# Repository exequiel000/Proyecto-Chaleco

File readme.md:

# VitalVest — Firmware (ESP32), pruebas y conexión con la app

Chaleco inteligente corrector de postura con monitoreo de **inclinación (grados)**, **pulsaciones (BPM)** y **temperatura (°C)**, conectado por Bluetooth (BLE) a la app VitalVest.

---

## 1. Cómo usar los códigos (Arduino IDE)

1. Descomprimir. Cada carpeta es un sketch: abrir el `.ino` que está adentro.
2. `Herramientas > Placa`: **ESP32 Dev Module**. Elegir el puerto COM.
3. Abrir el Monitor Serie a **115200** baudios.
4. Instalar las librerías (`Herramientas > Administrar bibliotecas`):
   - MPU6050 (Electronic Cats)
   - OneWire
   - DallasTemperature
   - SparkFun MAX3010x Pulse and Proximity Sensor Library

   La librería BLE ya viene con el soporte de placas ESP32.

### Orden recomendado de pruebas

| Carpeta | Qué prueba |
|---|---|
| `01_Test_I2C_Scanner` | Detecta el MPU6050 (0x68) y el MAX30102 (0x57) |
| `02_Test_MPU6050_Inclinacion` | Pitch, roll y desviación en grados + estado |
| `03_Test_DS18B20_Temperatura` | Temperatura en °C (`-127` = sensor sin conexión) |
| `04_Test_MAX30102_Pulso` | BPM, con el dedo apoyado sin apretar |
| `05_Test_Motor_Buzzer` | Verifica los transistores |
| `06_Test_Bateria` | Tensión y % de la batería 1S (comparar con multímetro) |
| `07_Test_BLE_Simulado` | Prueba la **app** sin necesitar sensores |
| `00_VitalVest_COMPLETO` | Firmware completo + BLE |

### Pines (según PCB)

| Función | Pin |
|---|---|
| I²C (MPU6050 y MAX30102) | SDA = GPIO21, SCL = GPIO22 |
| DS18B20 (OneWire) | GPIO19 |
| Buzzer (vía 2N2222F) | GPIO23 |
| Motor vibrador (vía MMBT2222A) | GPIO18 |
| Nivel de batería | GPIO34 |
| Recalibrar | BOOT = GPIO0 |

**Batería:** Li-ion 1S (3,0–4,2 V), divisor 100 kΩ / 100 kΩ y zener de 3,3 V como respaldo. El nodo llega como máximo a 2,1 V, por lo que el porcentaje es lineal en todo el rango.

---

## 2. Lógica de postura

La desviación es la mayor diferencia (pitch o roll) respecto de la postura calibrada.

| Estado | Desviación | Alerta |
|---|---|---|
| 🟢 Verde | < 20° | Ninguna |
| 🟡 Amarillo | 20°–30° | Motor 3 s cada 10 s + beep corto |
| 🔴 Rojo | > 30° | Motor y buzzer continuos |

- El estado debe mantenerse **500 ms** para cambiar (evita falsas alertas).
- **Recalibrar:** mantener BOOT 1 segundo, o enviar `"C"` desde la app.

---

## 3. Conexión chaleco ↔ app (BLE)

- Nombre del dispositivo: **`VitalVest`**
- Servicio: `12345678-1234-1234-1234-1234567890ab`
- Los datos viajan como **texto** y se envían cada 500 ms (notify).

| UUID termina en | Dato | Acceso | Formato | Uso en la app |
|---|---|---|---|---|
| `...1234567890ac` | Postura | notify | `"e,pitch,roll"` — e: 0 verde, 1 amarillo, 2 rojo. Ej: `"1,24.3,-3.1"` | Home / Posture (semáforo) |
| `...1234567890ad` | Temperatura | notify | `"36.5"` (°C) | Home / History |
| `...1234567890ae` | Pulsaciones | notify | `"75"` (0 = sin dedo) | Home / History |
| `...1234567890af` | Batería | notify | `"80"` (%) | Home / Settings |
| `...1234567890b0` | Comando | write | `"C"` | Botón "Recalibrar" |

**Cómo lo usa la app** (propuesta de diseño):

- **Home:** estado de postura con colores, BPM, temperatura y batería en tiempo real.
- **Posture (Analysis):** ángulos pitch y roll y desviación actual.
- **History:** lecturas guardadas para consultar por día (alertas, chequeos, mejoras).
- **Settings:** estado de conexión Bluetooth y nivel de batería.
- **Recalibrar:** la app escribe `"C"` en la característica de comando.

> Para probar la app sin chaleco, cargar el sketch `07_Test_BLE_Simulado`.
>
> En la versión web, Bluetooth funciona en **Chrome o Edge** (`localhost` cuenta como conexión segura). En Android usar Chrome.

---

## 4. La app VitalVest

**Diseño:** tema oscuro azul/cian, basado en 5 capturas (Login, Home, Posture Monitor, Health History, Settings).

**Secciones:** Home, Posture/Analysis, History, Settings (Timer previsto como función adicional).

### Acceso y cuenta (Firebase, proyecto "VitalVest")

- Inicio de sesión con **correo** y con **Google** (funcionando en local).
- "Olvidé mi contraseña": recuperación por correo.
- App web de Firebase ya registrada.

### Idiomas

Español por defecto + inglés, portugués, chino y tailandés, con opción **Automático** que usa el idioma del sistema del celular.

### Settings (decisiones tomadas)

- Botón **Edit**: cambia el nombre de usuario.
- Fila **Profile**: muestra el correo, permite cambiar la contraseña y ver/copiar el teléfono (solo lectura).
- Tema claro/oscuro, tamaño de letra, alto contraste.
- Notificaciones, avisos por voz, dispositivo, rendimiento, privacidad y permisos.

### Pestaña AI

Firebase AI Logic configurado, con App Check (reCAPTCHA Enterprise). La IA ya responde sin errores en localhost.

### Cómo correr la app en la PC (Windows)

- Versión offline: ejecutar `EJECUTAR.bat` (o `node server.js`) y abrir `http://localhost:8000`.
- Cuidado con la **carpeta doble** al descomprimir (OneDrive): entrar a la subcarpeta antes de ejecutar.
- Plan de pruebas: primero en PC (web), después en Android (web).
- Objetivo: que funcione en Android sin tener la terminal abierta.

---

## 5. Estado del proyecto

- ✅ **Hardware:** ESP32 + MPU6050 + DS18B20 + MAX30102 + motor + buzzer + batería 1S, según el diseño de PCB (3 versiones en KiCad).
- ✅ **MAX30102:** reemplazado y funcionando.
- ✅ **App:** funcionando y conectada al chaleco.

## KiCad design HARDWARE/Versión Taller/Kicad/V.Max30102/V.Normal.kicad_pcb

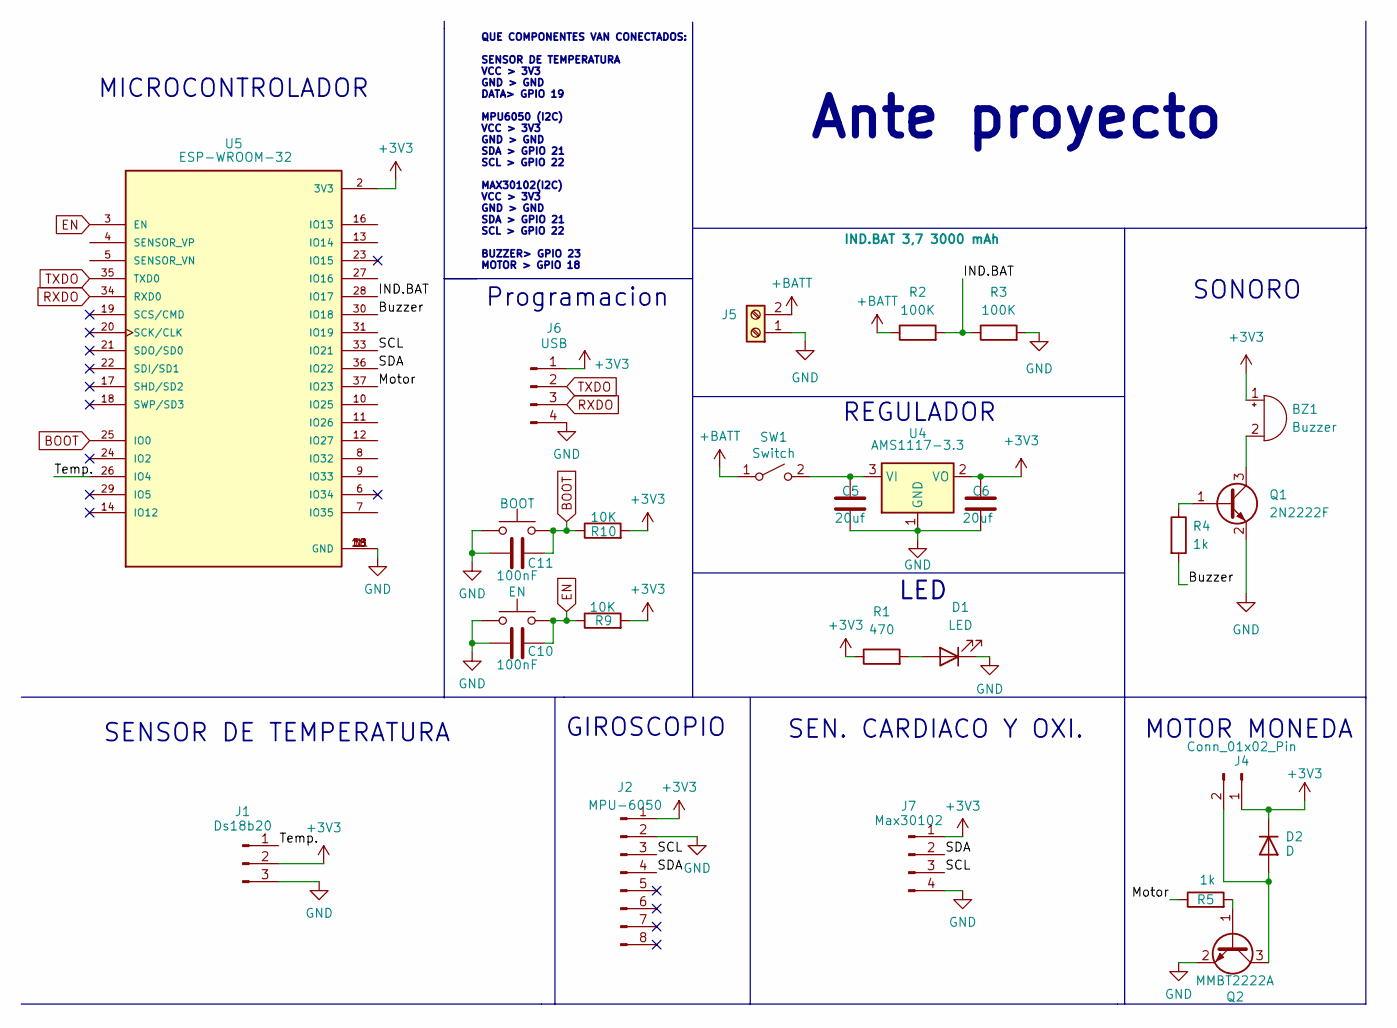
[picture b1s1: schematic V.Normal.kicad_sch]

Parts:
BZ1: Buzzer; MagneticBuzzer_PUI_AT-0927-TT-6-R
C5, C6: 20uf; C_0805_2012Metric_Pad1.18x1.45mm_HandSolder
C10, C11: 100nF; C_0805_2012Metric_Pad1.18x1.45mm_HandSolder
D1: LED; LED_0805_2012Metric_Pad1.15x1.40mm_HandSolder
D2: D; D_SMA
J1: Ds18b20; PinSocket_1x03_P2.54mm_Vertical
J2: MPU-6050; PinSocket_1x08_P2.54mm_Vertical
J4: Conn_01x02_Pin; PinSocket_1x02_P2.54mm_Vertical
J5: IND.BAT 3,7 3000 mAh; BORNERA2_AZUL
J6: USB; PinHeader_1x04_P2.54mm_Vertical
J7: Max30102; PinSocket_1x04_P2.54mm_Vertical
Q1: 2N2222F; SOT-23
Q2: MMBT2222A; SOT-23
R1: 470; R_0805_2012Metric_Pad1.20x1.40mm_HandSolder
R2, R3: 100K; R_0805_2012Metric_Pad1.20x1.40mm_HandSolder
R4, R5: 1k; R_0805_2012Metric_Pad1.20x1.40mm_HandSolder
R9, R10: 10K; R_0805_2012Metric_Pad1.20x1.40mm_HandSolder
SW1: Switch; BORNERA2_AZUL
SW3: EN; SW_PUSH_1P1T_6x3.5mm_H5.0_APEM_MJTP1250
SW4: BOOT; SW_PUSH_1P1T_6x3.5mm_H5.0_APEM_MJTP1250
U4: AMS1117-3.3; SOT-223-3_TabPin2
U5: ESP-WROOM-32; MODULE_ESP-WROOM-32

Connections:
+3V3: BZ1.1 (-), C6.1, D2.1 (K), J1.2, J2.1, J4.1, J6.1, J7.1, R1.1, R9.2, R10.2, U4.2 (VO), U5.2 (3V3)
+BATT: J5.2, R2.1, SW1.1 (A)
/Buzzer: R4.2, U5.30 (IO18)
/IND.BAT: R2.2, R3.1, U5.28 (IO17)
/Motor: R5.1, U5.37 (IO23)
/SCL: J2.3, J7.3, U5.33 (IO21)
/SDA: J2.4, J7.2, U5.36 (IO22)
/Temp.: J1.1, U5.26 (IO4)
BOOT: C11.1, R10.1, SW4.2, U5.25 (IO0)
EN: C10.1, R9.1, SW3.2, U5.3 (EN)
GND: C5.2, C6.2, C10.2, C11.2, D1.1 (K), J1.3, J2.2, J5.1, J6.4, J7.4, Q1.2 (E), Q2.2 (E), R3.2, SW3.1, SW4.1, U4.1 (GND), U5.1 (GND), U5.1.1 (GND), U5.15 (GND), U5.38 (GND)
unnamed: BZ1.2 (+), Q1.3 (C)
unnamed: D1.2 (A), R1.2
unnamed: D2.2 (A), J4.2, Q2.3 (C)
unnamed: Q1.1 (B), R4.1
unnamed: Q2.1 (B), R5.2
unnamed: C5.1, SW1.2 (B), U4.3 (VI)
RXDO: J6.3, U5.34 (RXD0)
TXDO: J6.2, U5.35 (TXD0)

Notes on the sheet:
SENSOR DE TEMPERATURA
QUE COMPONENTES VAN CONECTADOS: SENSOR DE TEMPERATURA VCC > 3V3 GND > GND DATA> GPIO 19 MPU6050 (I2C) VCC > 3V3 GND > GND SDA > GPIO 21 SCL > GPIO 22 MAX30102(I2C) VCC > 3V3 GND > GND SDA > GPIO 21 SCL > GPIO 22 BUZZER> GPIO 23 MOTOR > GPIO 18
Ante proyecto
MOTOR MONEDA
GIROSCOPIO
LED
Programacion
SEN. CARDIACO Y OXI.
REGULADOR
SONORO
MICROCONTROLADOR

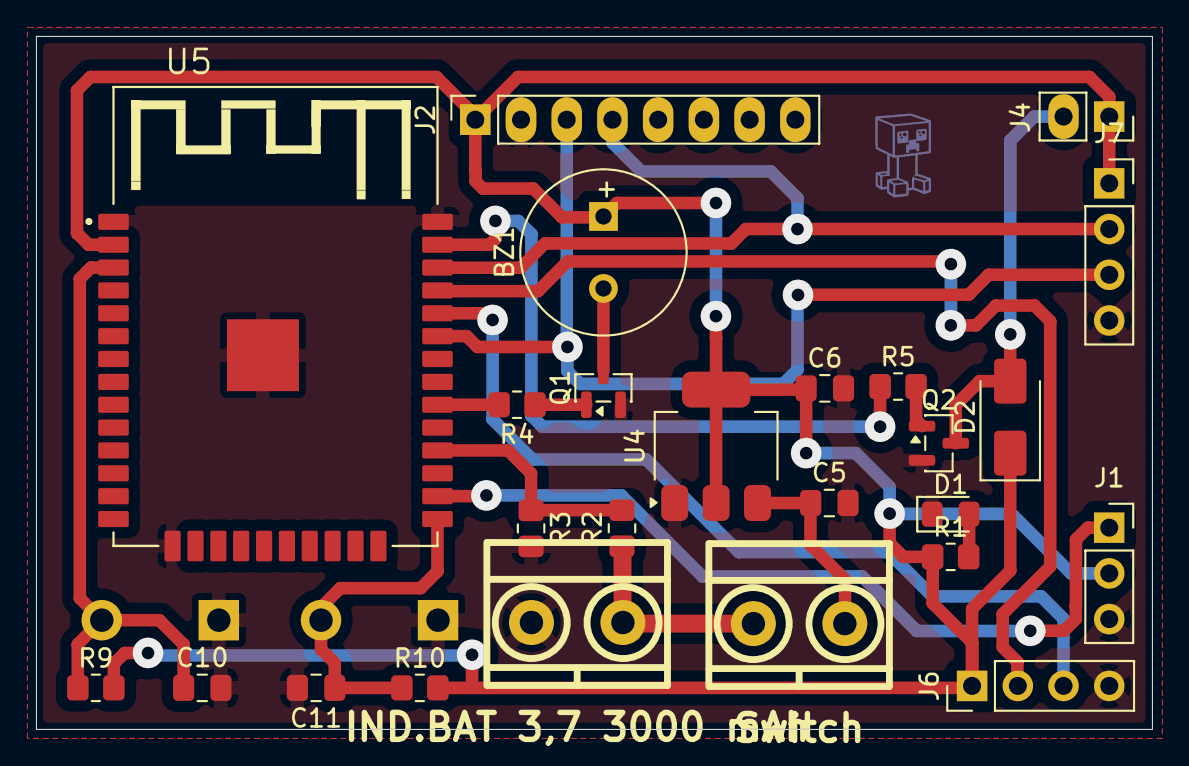
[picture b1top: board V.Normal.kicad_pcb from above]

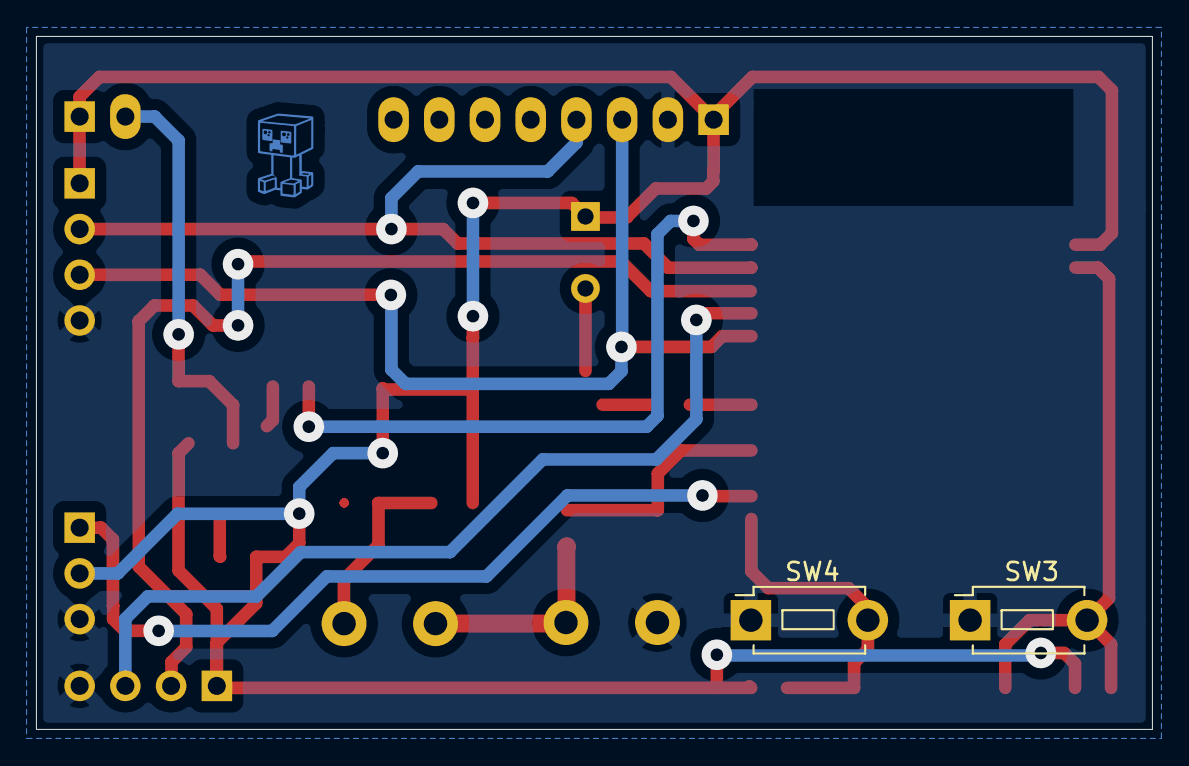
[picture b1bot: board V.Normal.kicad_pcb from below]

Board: 2 copper layers, 62.0 x 38.5 mm, 27 parts (2 on the bottom side), 19 nets.

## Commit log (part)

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2026-05-07 Final
2026-05-28 Parte Final
